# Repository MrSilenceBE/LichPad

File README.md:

# LichPad

# Description
The LichPad is a simple macropad with 9 keys, an OLED and an encoder so it can be used for multiple things.
Right now the script is very basic and I'm not sure if it will work but once i have it I will try to put more time in fixing it. I made the firmware with the help of a friend who has some experience with coding. For now it just acts as a numpad since the design reminds me of that but it will change. 
I made this to learn more about electronic projects such as PCB's and also to force myself to overcome certain challenges, and learn how to work with Fusion and KiCad. I will also force myself to learn how to program my project as soon as i get it and experiment with its capabilities. It has been very painful, but I learned a lot.

# BOM

1x Seeed XIAO RP2040

9x through-hole 1N4148 Diodes

9x MX-Style switches

1x EC11 Rotary encoders

1x 0.91 inch OLED display

9x white blank DSA keycaps

9x SK6812 MINI-E LEDs

4x M3x16mm screws

4x M3x5mx4mm heatset inserts

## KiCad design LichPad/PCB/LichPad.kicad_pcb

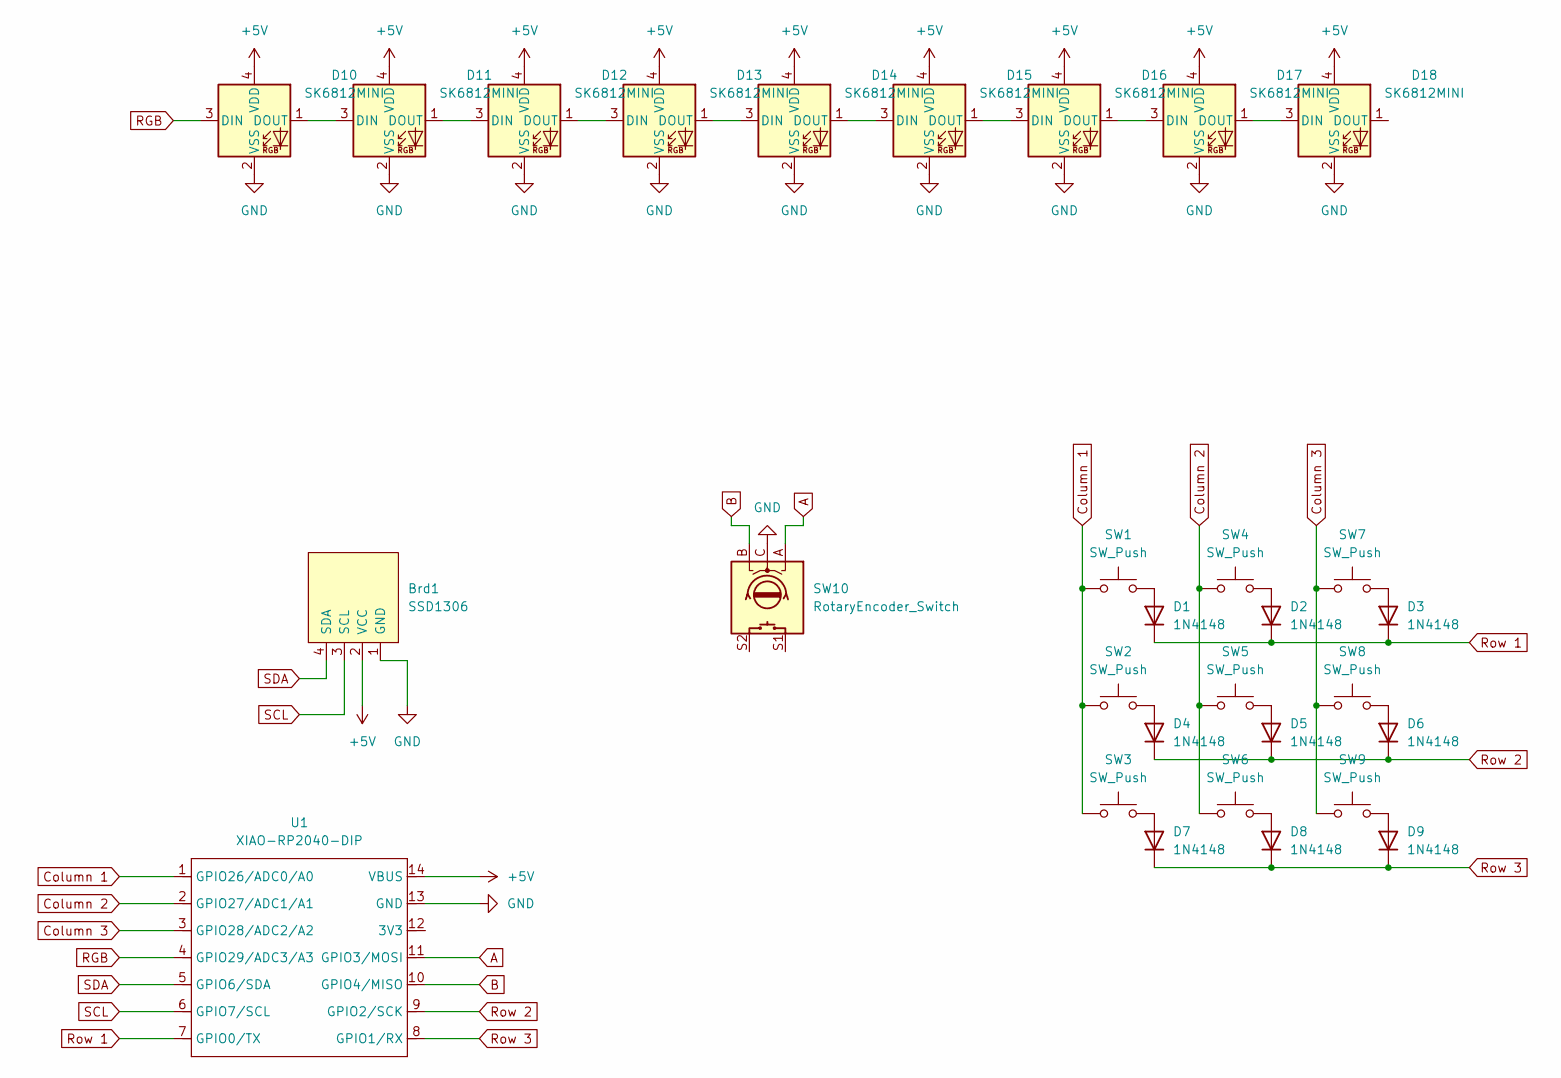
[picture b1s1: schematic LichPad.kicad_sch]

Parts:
Brd1: SSD1306; SSD1306-0.91-OLED-4pin-128x32
D1, D2, D3, D4, D5, D6, D7, D8, D9: 1N4148; D_DO-35_SOD27_P7.62mm_Horizontal
D10, D11, D12, D13, D14, D15, D16, D17, D18: SK6812MINI; LED_SK6812MINI_PLCC4_3.5x3.5mm_P1.75mm
SW1, SW2, SW3, SW4, SW5, SW6, SW7, SW8, SW9: SW_Push; SW_Cherry_MX_1.00u_PCB
SW10: RotaryEncoder_Switch; RotaryEncoder_Alps_EC11E-Switch_Vertical_H20mm
U1: XIAO-RP2040-DIP

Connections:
+5V: Brd1.2 (VCC), D10.4 (VDD), D11.4 (VDD), D12.4 (VDD), D13.4 (VDD), D14.4 (VDD), D15.4 (VDD), D16.4 (VDD), D17.4 (VDD), D18.4 (VDD), U1.14 (VBUS)
A: SW10.A, U1.11 (GPIO3/MOSI)
B: SW10.B, U1.10 (GPIO4/MISO)
Column 1: SW1.1, SW2.1, SW3.1, U1.1 (GPIO26/ADC0/A0)
Column 2: SW4.1, SW5.1, SW6.1, U1.2 (GPIO27/ADC1/A1)
Column 3: SW7.1, SW8.1, SW9.1, U1.3 (GPIO28/ADC2/A2)
GND: Brd1.1 (GND), D10.2 (VSS), D11.2 (VSS), D12.2 (VSS), D13.2 (VSS), D14.2 (VSS), D15.2 (VSS), D16.2 (VSS), D17.2 (VSS), D18.2 (VSS), SW10.C, U1.13 (GND)
unnamed: D1.2 (A), SW1.2
unnamed: D2.2 (A), SW4.2
unnamed: D3.2 (A), SW7.2
unnamed: D4.2 (A), SW2.2
unnamed: D5.2 (A), SW5.2
unnamed: D6.2 (A), SW8.2
unnamed: D7.2 (A), SW3.2
unnamed: D8.2 (A), SW6.2
unnamed: D9.2 (A), SW9.2
unnamed: D10.1 (DOUT), D11.3 (DIN)
unnamed: D11.1 (DOUT), D12.3 (DIN)
unnamed: D12.1 (DOUT), D13.3 (DIN)
unnamed: D13.1 (DOUT), D14.3 (DIN)
unnamed: D14.1 (DOUT), D15.3 (DIN)
unnamed: D15.1 (DOUT), D16.3 (DIN)
unnamed: D16.1 (DOUT), D17.3 (DIN)
unnamed: D17.1 (DOUT), D18.3 (DIN)
RGB: D10.3 (DIN), U1.4 (GPIO29/ADC3/A3)
Row 1: D1.1 (K), D2.1 (K), D3.1 (K), U1.7 (GPIO0/TX)
Row 2: D4.1 (K), D5.1 (K), D6.1 (K), U1.9 (GPIO2/SCK)
Row 3: D7.1 (K), D8.1 (K), D9.1 (K), U1.8 (GPIO1/RX)
SCL: Brd1.3 (SCL), U1.6 (GPIO7/SCL)
SDA: Brd1.4 (SDA), U1.5 (GPIO6/SDA)

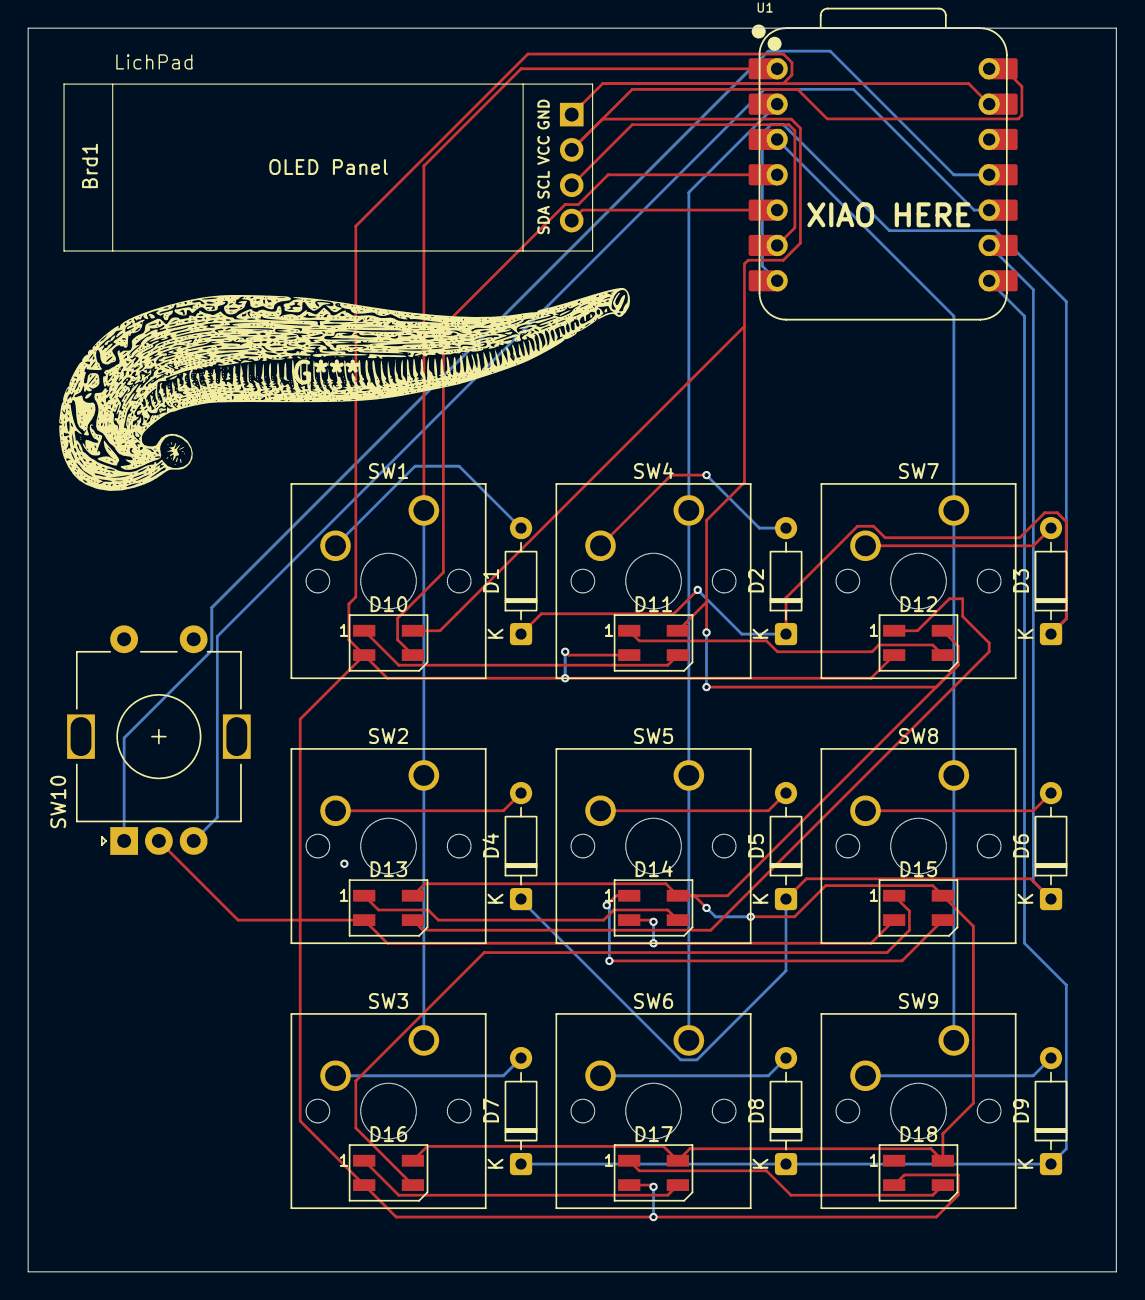
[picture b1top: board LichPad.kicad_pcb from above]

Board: 2 copper layers, 78.2 x 89.4 mm, 30 parts (0 on the bottom side), 30 nets.

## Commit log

2026-02-18 Update README with images and BOM information
    Added images and BOM details to the README.
2026-02-18 Update README.md with BOM details and images
2026-02-20 Add project description for LichPad macropad
    Added a project description for the LichPad macropad, detailing its features and development process.
